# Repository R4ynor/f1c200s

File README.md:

# f1c200s
 Just anothe F1C200S board

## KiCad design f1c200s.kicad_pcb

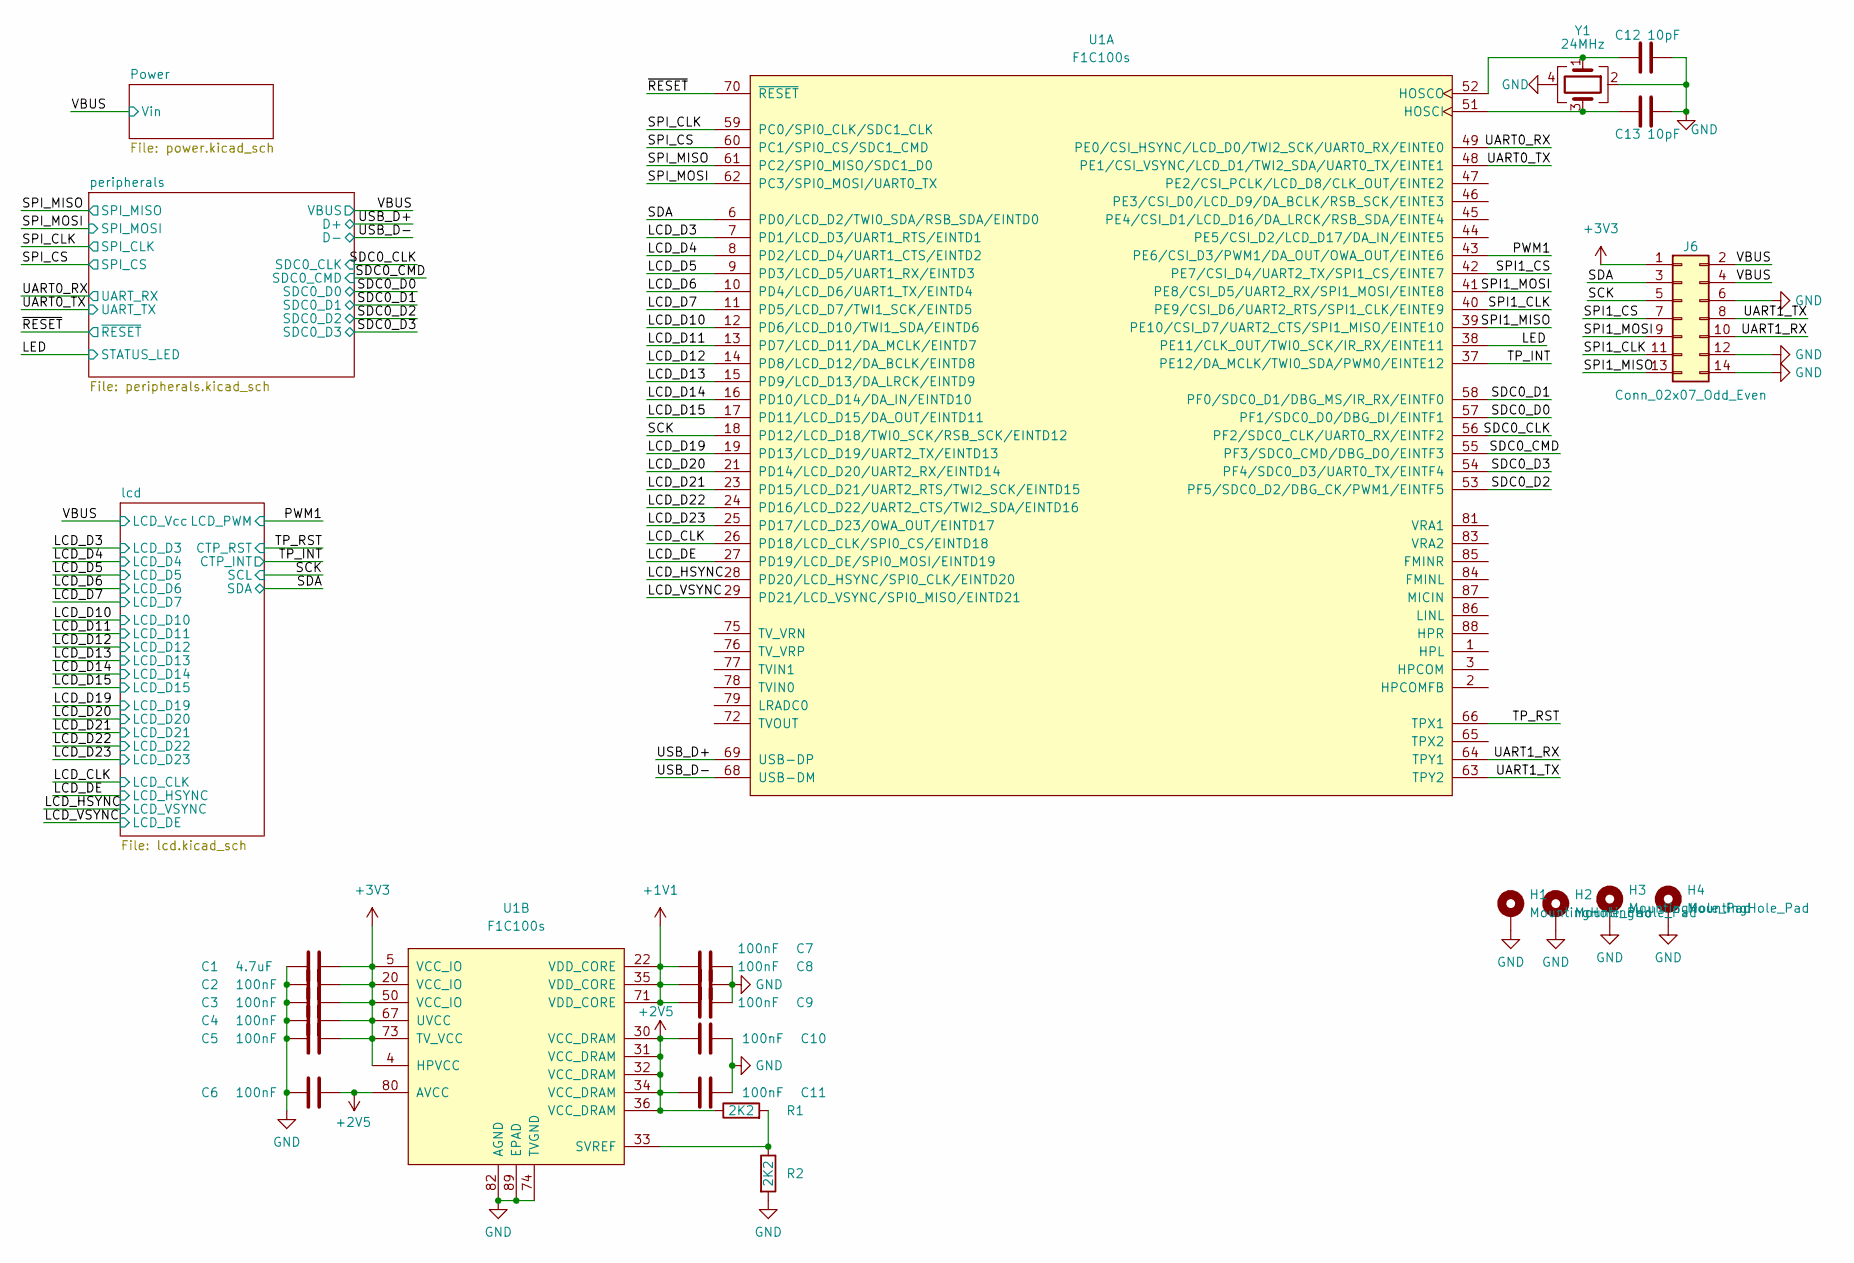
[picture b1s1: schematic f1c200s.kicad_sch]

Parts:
C1: 4.7uF; C_0603_1608Metric
C2, C3, C4, C5, C6, C7, C8, C9, C10, C11: 100nF; C_0603_1608Metric
C12, C13: 10pF; C_0603_1608Metric
H1, H2, H3, H4: MountingHole_Pad; MountingHole_2.2mm_M2_Pad_Via
J6: Conn_02x07_Odd_Even; PinHeader_2x07_P2.54mm_Vertical_SMD
R1, R2: 2K2; R_0603_1608Metric
U1: F1C100s; QFN-88_EP_10x10_Pitch0.4mm
Y1: 24MHz; Crystal_SMD_2520-4Pin_2.5x2.0mm

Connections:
+1V1: C7.2, C8.2, C9.2, U1.22 (VDD_CORE), U1.35 (VDD_CORE), U1.71 (VDD_CORE); also elsewhere on the board
+2V5: C6.2, C10.2, C11.2, R1.1, U1.30 (VCC_DRAM), U1.31 (VCC_DRAM), U1.32 (VCC_DRAM), U1.34 (VCC_DRAM), U1.36 (VCC_DRAM), U1.80 (AVCC); also elsewhere on the board
/LCD_CLK: U1.26 (PD18/LCD_CLK/SPI0_CS/EINTD18); also elsewhere on the board
/LCD_D3: U1.7 (PD1/LCD_D3/UART1_RTS/EINTD1); also elsewhere on the board
/LCD_D4: U1.8 (PD2/LCD_D4/UART1_CTS/EINTD2); also elsewhere on the board
/LCD_D5: U1.9 (PD3/LCD_D5/UART1_RX/EINTD3); also elsewhere on the board
/LCD_D6: U1.10 (PD4/LCD_D6/UART1_TX/EINTD4); also elsewhere on the board
/LCD_D7: U1.11 (PD5/LCD_D7/TWI1_SCK/EINTD5); also elsewhere on the board
/LCD_D10: U1.12 (PD6/LCD_D10/TWI1_SDA/EINTD6); also elsewhere on the board
/LCD_D11: U1.13 (PD7/LCD_D11/DA_MCLK/EINTD7); also elsewhere on the board
/LCD_D12: U1.14 (PD8/LCD_D12/DA_BCLK/EINTD8); also elsewhere on the board
/LCD_D13: U1.15 (PD9/LCD_D13/DA_LRCK/EINTD9); also elsewhere on the board
/LCD_D14: U1.16 (PD10/LCD_D14/DA_IN/EINTD10); also elsewhere on the board
/LCD_D15: U1.17 (PD11/LCD_D15/DA_OUT/EINTD11); also elsewhere on the board
/LCD_D19: U1.19 (PD13/LCD_D19/UART2_TX/EINTD13); also elsewhere on the board
/LCD_D20: U1.21 (PD14/LCD_D20/UART2_RX/EINTD14); also elsewhere on the board
/LCD_D21: U1.23 (PD15/LCD_D21/UART2_RTS/TWI2_SCK/EINTD15); also elsewhere on the board
/LCD_D22: U1.24 (PD16/LCD_D22/UART2_CTS/TWI2_SDA/EINTD16); also elsewhere on the board
/LCD_D23: U1.25 (PD17/LCD_D23/OWA_OUT/EINTD17); also elsewhere on the board
/LCD_DE: U1.27 (PD19/LCD_DE/SPI0_MOSI/EINTD19); also elsewhere on the board
/LCD_HSYNC: U1.28 (PD20/LCD_HSYNC/SPI0_CLK/EINTD20); also elsewhere on the board
/LCD_VSYNC: U1.29 (PD21/LCD_VSYNC/SPI0_MISO/EINTD21); also elsewhere on the board
/LED: U1.38 (PE11/CLK_OUT/TWI0_SCK/IR_RX/EINTE11); also elsewhere on the board
/PWM1: U1.43 (PE6/CSI_D3/PWM1/DA_OUT/OWA_OUT/EINTE6); also elsewhere on the board
/SCK: J6.5, U1.18 (PD12/LCD_D18/TWI0_SCK/RSB_SCK/EINTD12); also elsewhere on the board
/SDA: J6.3, U1.6 (PD0/LCD_D2/TWI0_SDA/RSB_SDA/EINTD0); also elsewhere on the board
/SDC0_CLK: U1.56 (PF2/SDC0_CLK/UART0_RX/EINTF2); also elsewhere on the board
/SDC0_CMD: U1.55 (PF3/SDC0_CMD/DBG_DO/EINTF3); also elsewhere on the board
/SDC0_D0: U1.57 (PF1/SDC0_D0/DBG_DI/EINTF1); also elsewhere on the board
/SDC0_D1: U1.58 (PF0/SDC0_D1/DBG_MS/IR_RX/EINTF0); also elsewhere on the board
/SDC0_D2: U1.53 (PF5/SDC0_D2/DBG_CK/PWM1/EINTF5); also elsewhere on the board
/SDC0_D3: U1.54 (PF4/SDC0_D3/UART0_TX/EINTF4); also elsewhere on the board
/SPI1_CLK: J6.11, U1.40 (PE9/CSI_D6/UART2_RTS/SPI1_CLK/EINTE9)
/SPI1_CS: J6.7, U1.42 (PE7/CSI_D4/UART2_TX/SPI1_CS/EINTE7)
/SPI1_MISO: J6.13, U1.39 (PE10/CSI_D7/UART2_CTS/SPI1_MISO/EINTE10)
/SPI1_MOSI: J6.9, U1.41 (PE8/CSI_D5/UART2_RX/SPI1_MOSI/EINTE8)
/SPI_CLK: U1.59 (PC0/SPI0_CLK/SDC1_CLK); also elsewhere on the board
/SPI_CS: U1.60 (PC1/SPI0_CS/SDC1_CMD); also elsewhere on the board
/SPI_MISO: U1.61 (PC2/SPI0_MISO/SDC1_D0); also elsewhere on the board
/SPI_MOSI: U1.62 (PC3/SPI0_MOSI/UART0_TX); also elsewhere on the board
/TP_INT: U1.37 (PE12/DA_MCLK/TWI0_SDA/PWM0/EINTE12); also elsewhere on the board
/TP_RST: U1.66 (TPX1); also elsewhere on the board
/UART0_RX: U1.49 (PE0/CSI_HSYNC/LCD_D0/TWI2_SCK/UART0_RX/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); also elsewhere on the board
/UART0_TX: U1.48 (PE1/CSI_VSYNC/LCD_D1/TWI2_SDA/UART0_TX/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); also elsewhere on the board
/UART1_RX: J6.10, U1.64 (TPY1)
/UART1_TX: J6.8, U1.63 (TPY2)
/USB_D+: U1.69 (USB-DP); also elsewhere on the board
/USB_D-: U1.68 (USB-DM); also elsewhere on the board
/VBUS: J6.2, J6.4; also elsewhere on the board
/~RESET: U1.70 (~RESET); also elsewhere on the board
AGND: C1.1, C2.1, C3.1, C4.1, C5.1, C6.1, C7.1, C8.1, C9.1, C10.1, C11.1, C12.2, C13.2, H1.1, H2.1, H3.1, H4.1, J6.6, J6.12, J6.14, R2.2, U1.74 (TVGND), U1.82 (AGND), U1.89 (EPAD), Y1.2, Y1.4; also elsewhere on the board
unnamed: C12.1, U1.52 (HOSCO), Y1.1
unnamed: C13.1, U1.51 (HOSCI), Y1.3
unnamed: R1.2, R2.1, U1.33 (SVREF)

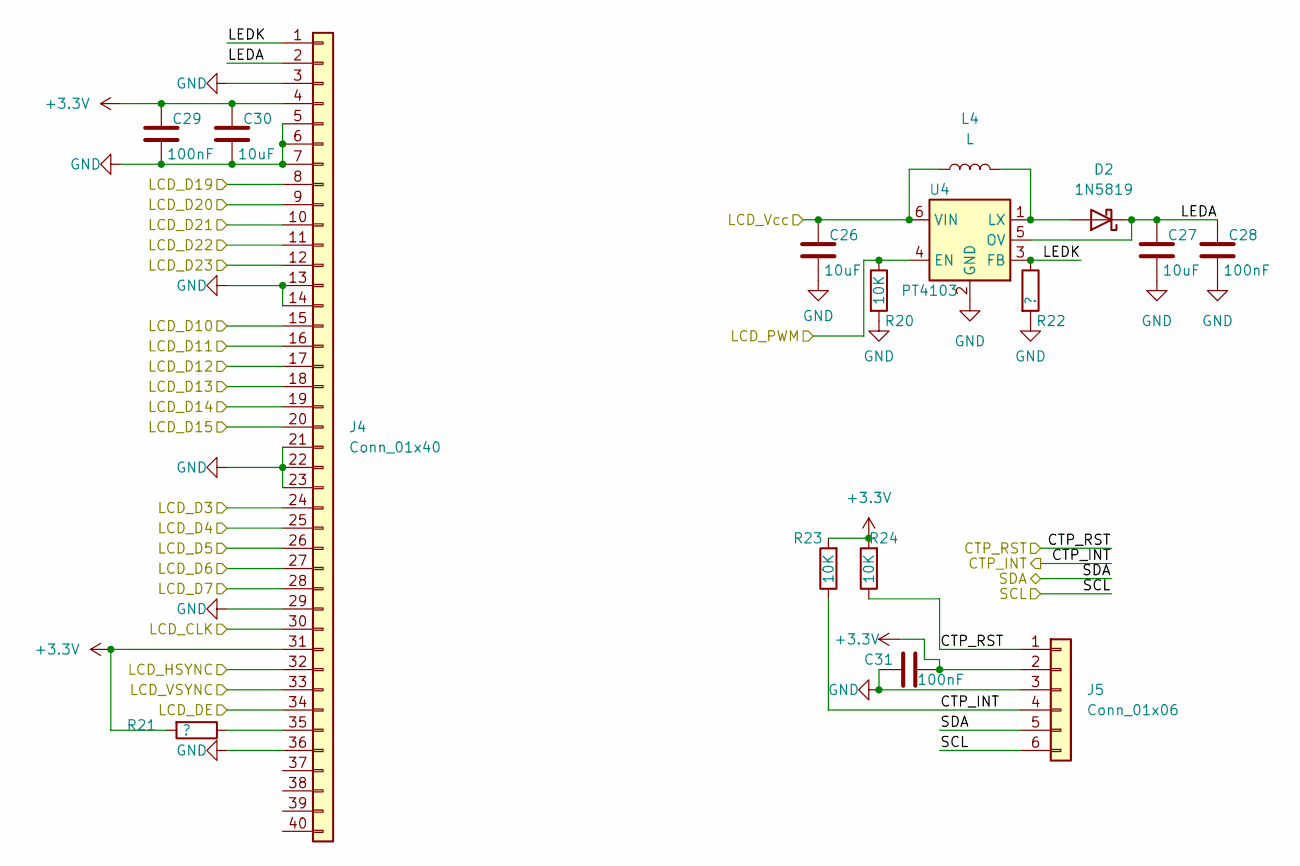
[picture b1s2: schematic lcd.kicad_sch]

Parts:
C26, C27, C30: 10uF; C_0603_1608Metric
C28, C29, C31: 100nF; C_0603_1608Metric
D2: 1N5819; D_SOD-123
J4: Conn_01x40; 40PIN_XKB_X05A15L40T
J5: Conn_01x06; 6PIN_XKB_X05A20L06T
L4: L; L_1008_2520Metric
R20, R23, R24: 10K; R_0603_1608Metric
R21, R22: ?; R_0603_1608Metric
U4: PT4103; SOT-23-6

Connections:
/LCD_CLK: J4.30; also elsewhere on the board
/LCD_D3: J4.24; also elsewhere on the board
/LCD_D4: J4.25; also elsewhere on the board
/LCD_D5: J4.26; also elsewhere on the board
/LCD_D6: J4.27; also elsewhere on the board
/LCD_D7: J4.28; also elsewhere on the board
/LCD_D10: J4.15; also elsewhere on the board
/LCD_D11: J4.16; also elsewhere on the board
/LCD_D12: J4.17; also elsewhere on the board
/LCD_D13: J4.18; also elsewhere on the board
/LCD_D14: J4.19; also elsewhere on the board
/LCD_D15: J4.20; also elsewhere on the board
/LCD_D19: J4.8; also elsewhere on the board
/LCD_D20: J4.9; also elsewhere on the board
/LCD_D21: J4.10; also elsewhere on the board
/LCD_D22: J4.11; also elsewhere on the board
/LCD_D23: J4.12; also elsewhere on the board
/LCD_DE: J4.32; also elsewhere on the board
/LCD_HSYNC: J4.33; also elsewhere on the board
/LCD_VSYNC: J4.34; also elsewhere on the board
/PWM1: R20.1, U4.4 (EN); also elsewhere on the board
/SCK: J5.6; also elsewhere on the board
/SDA: J5.5; also elsewhere on the board
/TP_INT: J5.4, R23.1; also elsewhere on the board
/TP_RST: J5.1, R24.1; also elsewhere on the board
/VBUS: C26.1, L4.1, U4.6 (VIN); also elsewhere on the board
/lcd/LEDA: C27.1, C28.1, D2.1 (K), J4.2, U4.5 (OV)
/lcd/LEDK: J4.1, R22.1, U4.3 (FB)
AGND: C26.2, C27.2, C28.2, C29.2, C30.2, C31.1, J4.3, J4.5, J4.6, J4.7, J4.13, J4.14, J4.21, J4.22, J4.23, J4.29, J4.36, J5.3, R20.2, R22.2, U4.2 (GND); also elsewhere on the board
unnamed: D2.2 (A), L4.2, U4.1 (LX)
unnamed: J4.35, R21.1

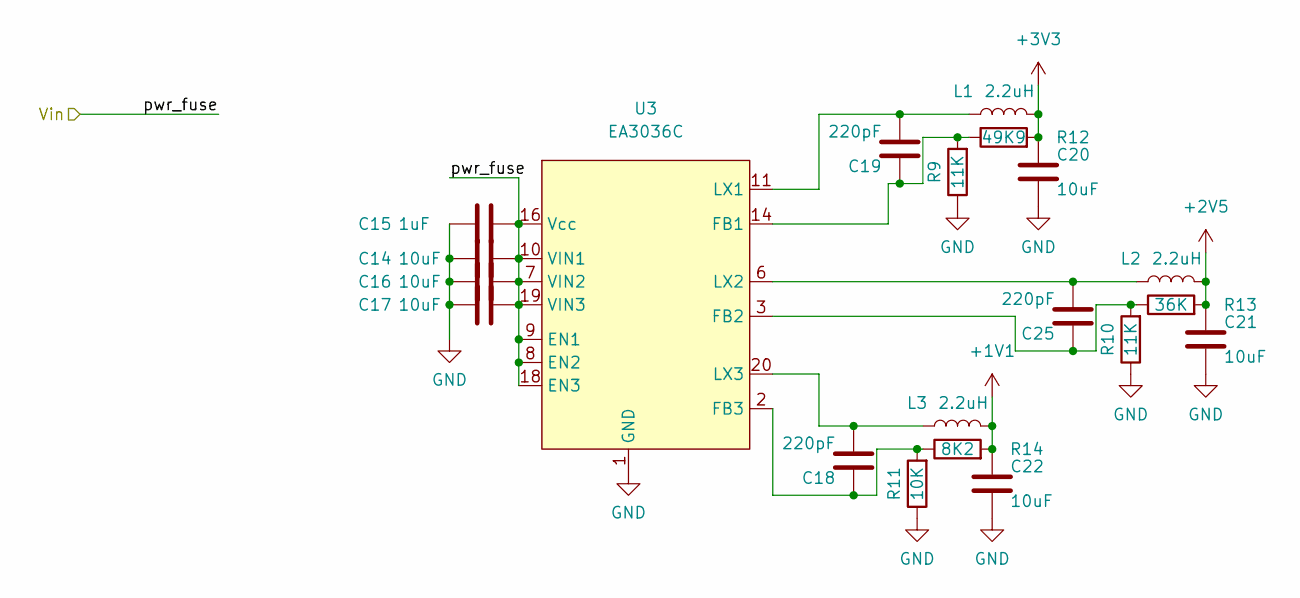
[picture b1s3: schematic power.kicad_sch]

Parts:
C14, C16, C17, C20, C21, C22: 10uF; C_0603_1608Metric
C15: 1uF; C_0603_1608Metric
C18, C19, C25: 220pF; C_0603_1608Metric
L1, L2, L3: 2.2uH; L_1008_2520Metric
R9, R10: 11K; R_0603_1608Metric
R11: 10K; R_0603_1608Metric
R12: 49K9; R_0603_1608Metric
R13: 36K; R_0603_1608Metric
R14: 8K2; R_0603_1608Metric
U3: EA3036C; QFN-20-1EP_3x3mm_P0.4mm_EP1.65x1.65mm

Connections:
+1V1: C22.1, L3.2, R14.2; also elsewhere on the board
+2V5: C21.1, L2.2, R13.2; also elsewhere on the board
/VBUS: C14.1, C15.1, C16.1, C17.1, U3.7 (VIN2), U3.8 (EN2), U3.9 (EN1), U3.10 (VIN1), U3.16 (Vcc), U3.18 (EN3), U3.19 (VIN3); also elsewhere on the board
AGND: C14.2, C15.2, C16.2, C17.2, C20.2, C21.2, C22.2, R9.1, R10.1, R11.1, U3.1 (GND), U3.4 (GND), U3.5 (GND), U3.12 (GND), U3.13 (GND), U3.15 (GND), U3.17 (AGND), U3.21 (GND); also elsewhere on the board
unnamed: C18.1, R11.2, R14.1, U3.2 (FB3)
unnamed: C18.2, L3.1, U3.20 (LX3)
unnamed: C19.1, R9.2, R12.1, U3.14 (FB1)
unnamed: C19.2, L1.1, U3.11 (LX1)
unnamed: C25.1, R10.2, R13.1, U3.3 (FB2)
unnamed: C25.2, L2.1, U3.6 (LX2)

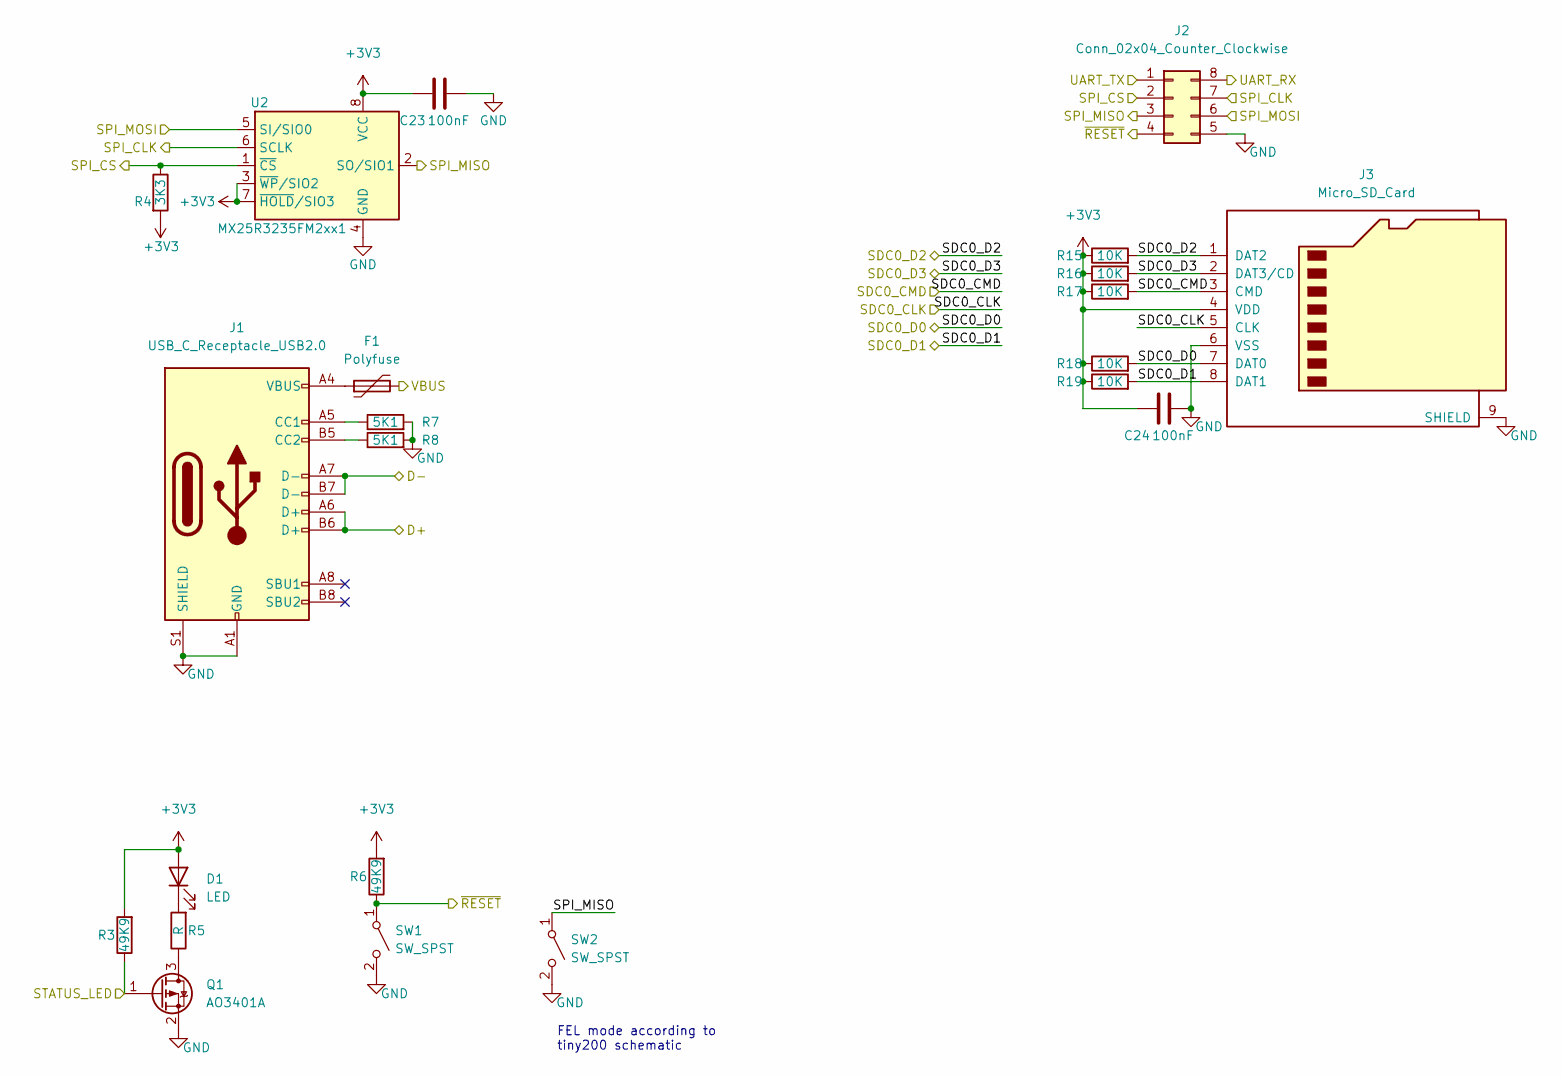
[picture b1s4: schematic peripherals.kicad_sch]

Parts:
C23, C24: 100nF; C_0603_1608Metric
D1: LED; LED_0603_1608Metric
F1: Polyfuse; R_0603_1608Metric
J1: USB_C_Receptacle_USB2.0; USB_C_Receptacle_XKB_U262-16XN-4BVC11
J2: Conn_02x04_Counter_Clockwise; SOIC_clipProgSmall
J3: Micro_SD_Card; TF-CARD_XKTF-0803-0
Q1: AO3401A; SOT-23
R3, R6: 49K9; R_0603_1608Metric
R4: 3K3; R_0603_1608Metric
R5: R; R_0603_1608Metric
R7, R8: 5K1; R_0603_1608Metric
R15, R16, R17, R18, R19: 10K; R_0603_1608Metric
SW1, SW2: SW_SPST; SW_3x4x2
U2: MX25R3235FM2xx1; SOP-8_5.28x5.23mm_P1.27mm

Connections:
/LED: Q1.1 (G), R3.1; also elsewhere on the board
/SDC0_CLK: J3.5 (CLK); also elsewhere on the board
/SDC0_CMD: J3.3 (CMD), R17.2; also elsewhere on the board
/SDC0_D0: J3.7 (DAT0), R18.2; also elsewhere on the board
/SDC0_D1: J3.8 (DAT1), R19.2; also elsewhere on the board
/SDC0_D2: J3.1 (DAT2), R15.2; also elsewhere on the board
/SDC0_D3: J3.2 (DAT3/CD), R16.2; also elsewhere on the board
/SPI_CLK: J2.7, U2.6 (SCLK); also elsewhere on the board
/SPI_CS: J2.2, R4.1, U2.1 (~CS); also elsewhere on the board
/SPI_MISO: J2.3, SW2.1 (A), U2.2 (SO/SIO1); also elsewhere on the board
/SPI_MOSI: J2.6, U2.5 (SI/SIO0); also elsewhere on the board
/UART0_RX: J2.8; also elsewhere on the board
/UART0_TX: J2.1; also elsewhere on the board
/USB_D+: J1.A6 (D+), J1.B6 (D+); also elsewhere on the board
/USB_D-: J1.A7 (D-), J1.B7 (D-); also elsewhere on the board
/VBUS: F1.2; also elsewhere on the board
/~RESET: J2.4, R6.1, SW1.1 (A); also elsewhere on the board
AGND: C23.2, C24.2, J1.A1 (GND), J1.A12 (GND), J1.B1 (GND), J1.B12 (GND), J1.S1 (SHIELD), J2.5, J3.6 (VSS), J3.9 (SHIELD), Q1.2 (S), R7.2, R8.2, SW1.2 (B), SW2.2 (B), U2.4 (GND); also elsewhere on the board
unnamed: D1.1 (K), R5.2
unnamed: F1.1, J1.A4 (VBUS), J1.A9 (VBUS), J1.B4 (VBUS), J1.B9 (VBUS)
unnamed: J1.A5 (CC1), R7.1
unnamed: J1.B5 (CC2), R8.1
unnamed: Q1.3 (D), R5.1

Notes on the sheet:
FEL mode according to tiny200 schematic

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
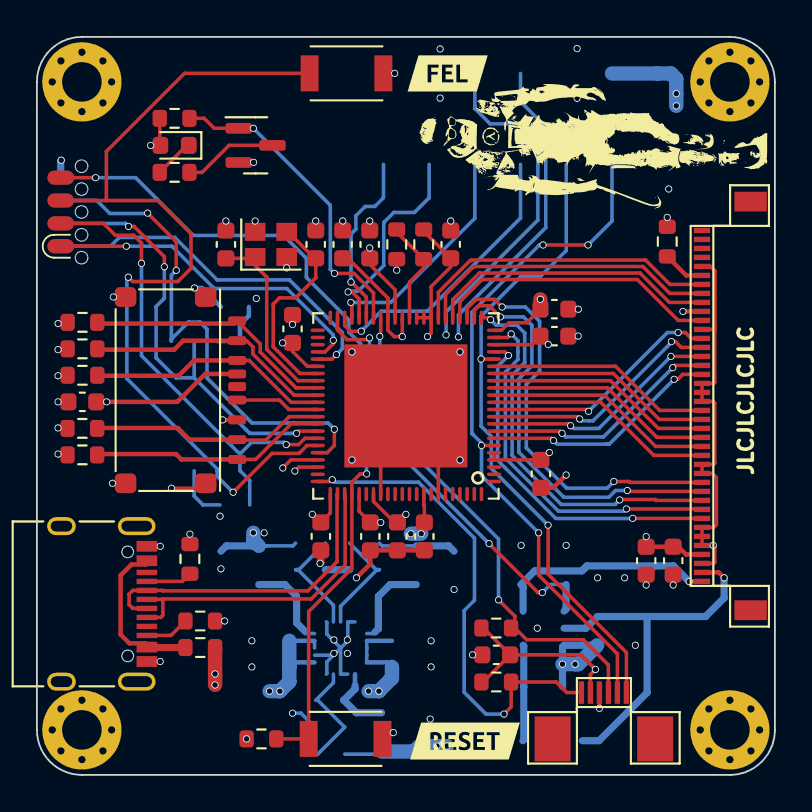
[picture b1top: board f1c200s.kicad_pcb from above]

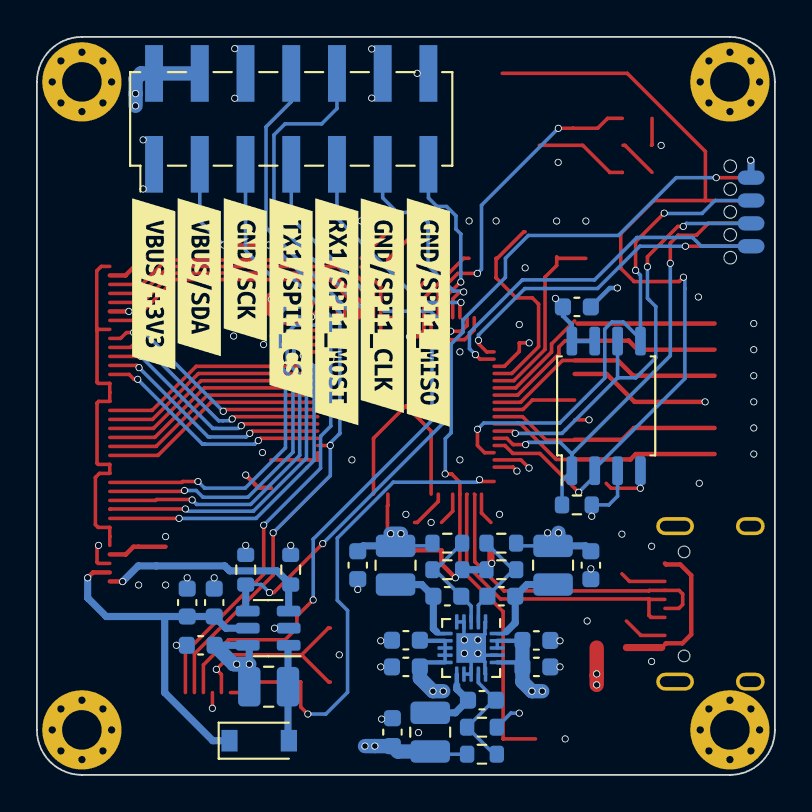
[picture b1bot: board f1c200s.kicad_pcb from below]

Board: 4 copper layers, 41.0 x 41.0 mm, 89 parts (39 on the bottom side), 70 nets.

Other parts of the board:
kibuzzard-61F2B632: G***; kibuzzard-61F2B632
kibuzzard-61F42E62: G***; kibuzzard-61F42E62
kibuzzard-61F42E89: G***; kibuzzard-61F42E89
kibuzzard-61F42EC1: G***; kibuzzard-61F42EC1
kibuzzard-61F42F71: G***; kibuzzard-61F42F71
kibuzzard-61F331AB: G***; kibuzzard-61F331AB
kibuzzard-61F430B6: G***; kibuzzard-61F430B6
kibuzzard-61F430D1: G***; kibuzzard-61F430D1
kibuzzard-61F43008: G***; kibuzzard-61F43008
